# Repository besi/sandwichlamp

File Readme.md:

# Sandwich Lamp

## Pinout

| Pin | Function     |
|-----|--------------|
| 13  | Enable 12V   |
| 18  | Neopixel     |
| 14  | Touch 1      |
| 32  | Touch 2      |
| 4   | Touch 3      |
| 34  | Button 1     |
| 33  | Button 2     |
| 39  | Button 3     |
| 36  | Button 4     |
| 35  | Button X     |
| 27  | Radar TX     |
| 12  | Radar RX     |
| 19  | I2C SCL      |
| 23  | I2C SDA      |
| 16  | Battery Sens |
| 2   | Brightness   |
| 5   | Onboard LED  |
| 0   | OneWire      |

## Installation

```
import mip
mip.install("github:robert-hh/BME280")
```

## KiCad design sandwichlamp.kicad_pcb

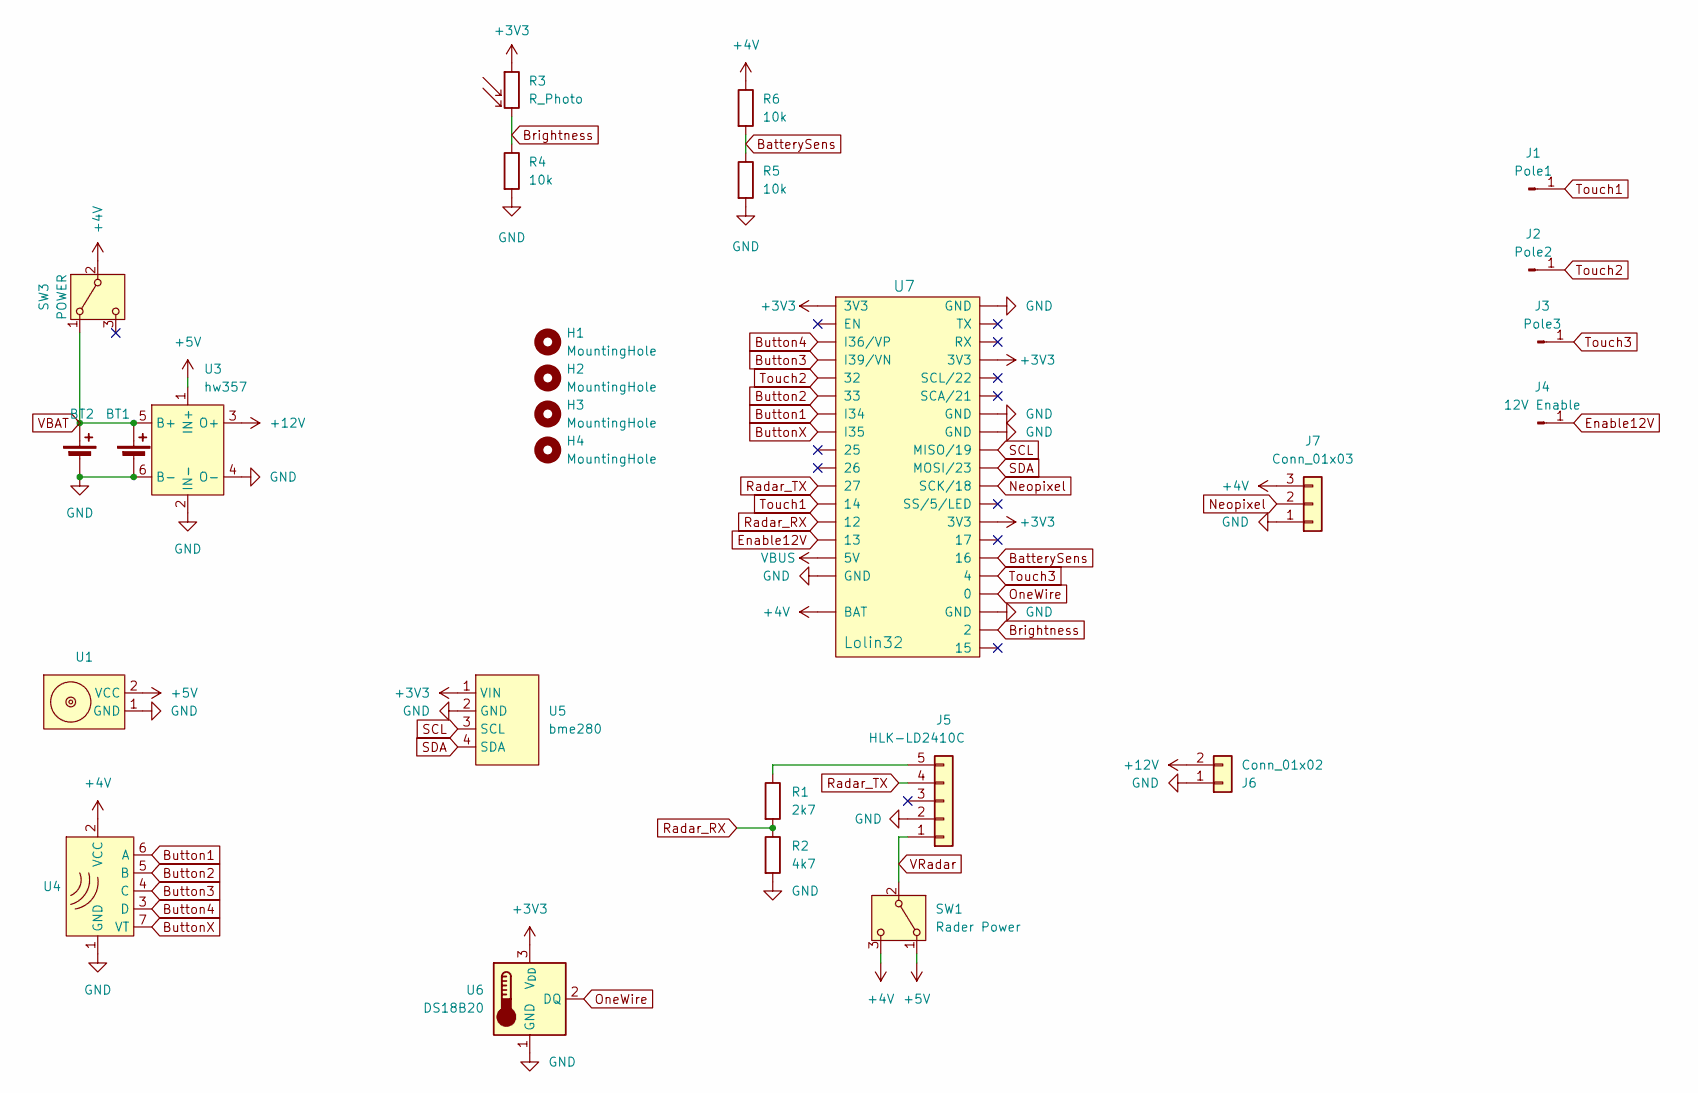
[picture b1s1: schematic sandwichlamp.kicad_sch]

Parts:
BT1: Battery_Cell; JST_PH_S2B-PH-SM4-TB_1x02-1MP_P2.00mm_Horizontal
BT2: Battery_Cell; JST_PH_B2B-PH-K_1x02_P2.00mm_Vertical
H1, H2, H3, H4: MountingHole; MountingHole_3.2mm_M3
J1: Pole1; MountingHole_4.3mm_M4_ISO7380_Pad_TopOnly
J2: Pole2; MountingHole_4.3mm_M4_ISO7380_Pad_TopOnly
J3: Pole3; MountingHole_4.3mm_M4_ISO7380_Pad_TopOnly
J4: 12V Enable; PinHeader_1x01_P2.54mm_Vertical
J5: HLK-LD2410C; PinHeader_1x05_P2.54mm_Vertical
J6: Conn_01x02; PinHeader_1x02_P2.54mm_Vertical
J7: Conn_01x03; PinHeader_1x03_P2.54mm_Vertical
R1: 2k7; R_Axial_DIN0207_L6.3mm_D2.5mm_P7.62mm_Horizontal
R2: 4k7; R_Axial_DIN0207_L6.3mm_D2.5mm_P7.62mm_Horizontal
R3: R_Photo; R_LDR_5.0x4.1mm_P3mm_Vertical
R4, R5, R6: 10k; R_0805_2012Metric_Pad1.20x1.40mm_HandSolder
SW1: Rader Power; PinHeader_1x03_P2.54mm_Vertical
SW3: POWER; as12ap
U1: magnetic-charger
U3: hw357
U4: RX480E; radio-receiver
U5: bme280
U6: DS18B20; TO-92L_Inline_Wide
U7: Lolin32; lolin32

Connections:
+3V3: R3.1, U5.1 (VIN), U6.3 (V_{DD}), U7.1 (3V3), U7.20 (3V3), U7.29 (3V3)
+4V: J7.3, R6.1, SW1.3 (C), SW3.2 (B), U4.2 (VCC), U7.37 (BAT)
+5V: SW1.1 (A), U1.2 (VCC), U3.1 (IN+)
+12V: J6.2, U3.3 (O+)
BatterySens: R5.1, R6.2, U7.31 (16)
Brightness: R3.2, R4.1, U7.35 (2)
Button1: U4.6 (A), U7.7 (I34)
Button2: U4.5 (B), U7.6 (33)
Button3: U4.4 (C), U7.4 (I39/VN)
Button4: U4.3 (D), U7.3 (I36/VP)
ButtonX: U4.7 (VT), U7.8 (I35)
Enable12V: J4.1, U7.14 (13)
GND: BT1.1 (-), BT2.2 (-), J5.2, J6.1, J7.1, R2.2, R4.2, R5.2, U1.1 (GND), U3.2 (IN-), U3.4 (O-), U3.6 (B-), U4.1 (GND), U5.2 (GND), U6.1 (GND), U7.16 (GND), U7.17 (GND), U7.23 (GND), U7.24 (GND), U7.34 (GND)
Neopixel: J7.2, U7.27 (SCK/18)
unnamed: J5.5, R1.1
OneWire: U6.2 (DQ), U7.33 (0)
Radar_RX: R1.2, R2.1, U7.13 (12)
Radar_TX: J5.4, U7.11 (27)
SCL: U5.3 (SCL), U7.25 (MISO/19)
SDA: U5.4 (SDA), U7.26 (MOSI/23)
Touch1: J1.1, U7.12 (14)
Touch2: J2.1, U7.5 (32)
Touch3: J3.1, U7.32 (4)
VBAT: BT1.2 (+), BT2.1 (+), SW3.1 (A), U3.5 (B+)
VBUS: U7.15 (5V)
VRadar: J5.1, SW1.2 (B)

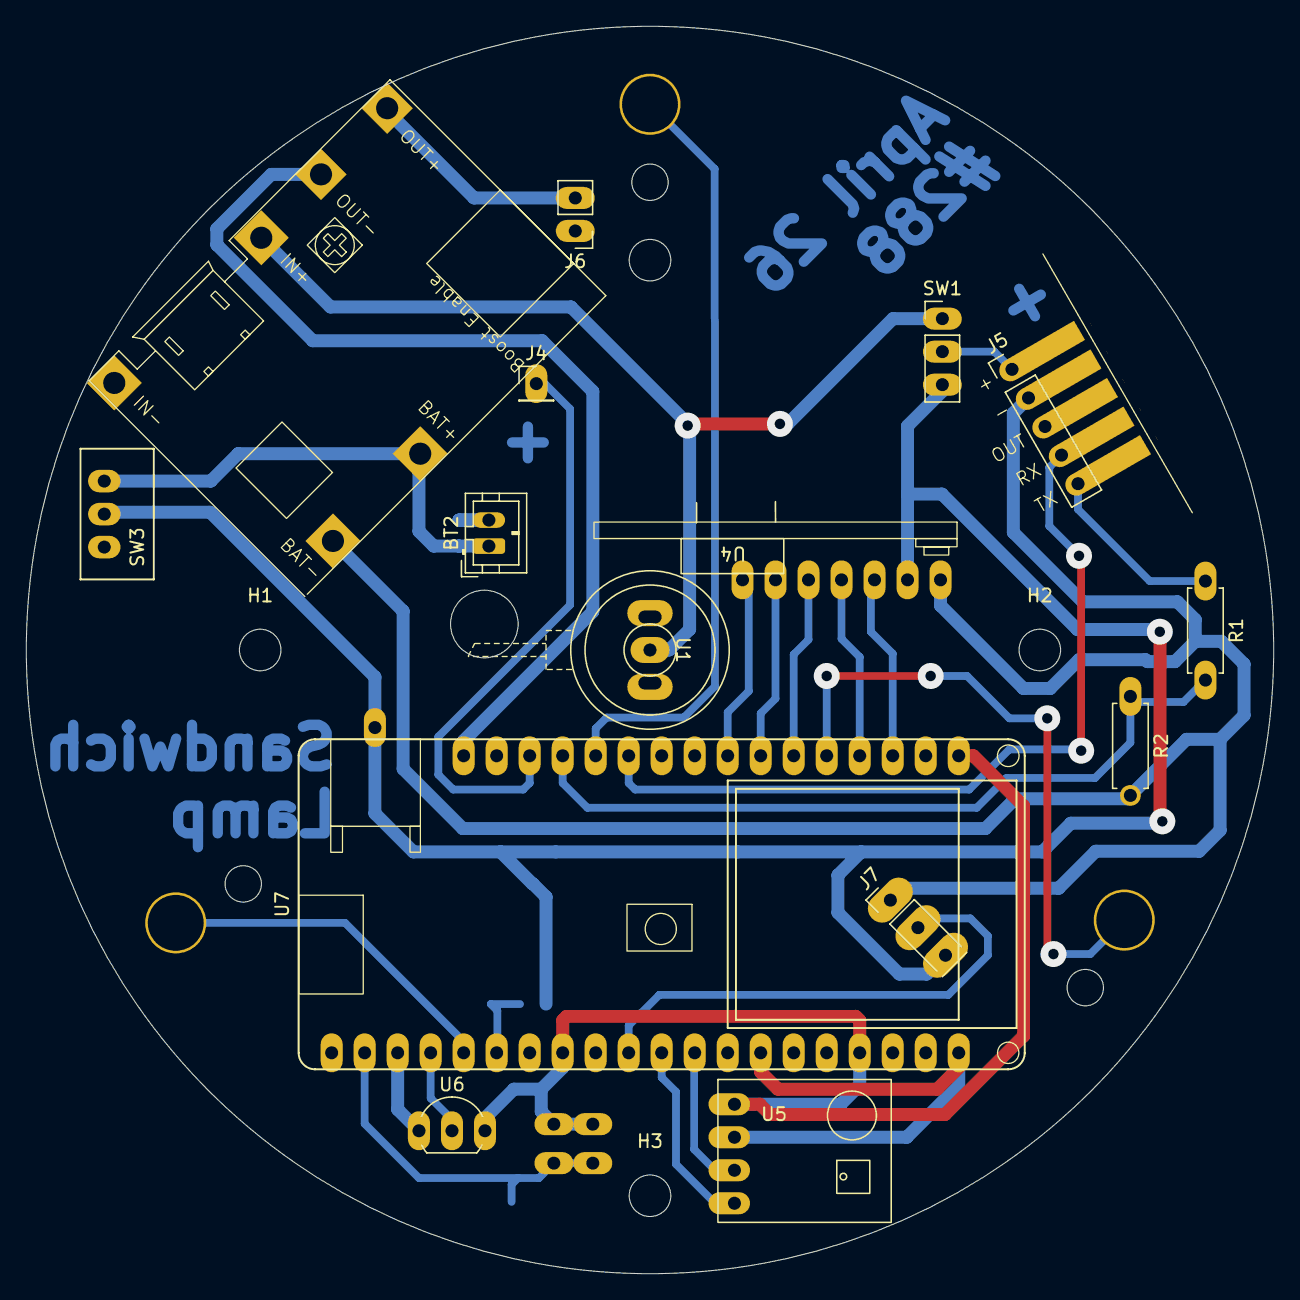
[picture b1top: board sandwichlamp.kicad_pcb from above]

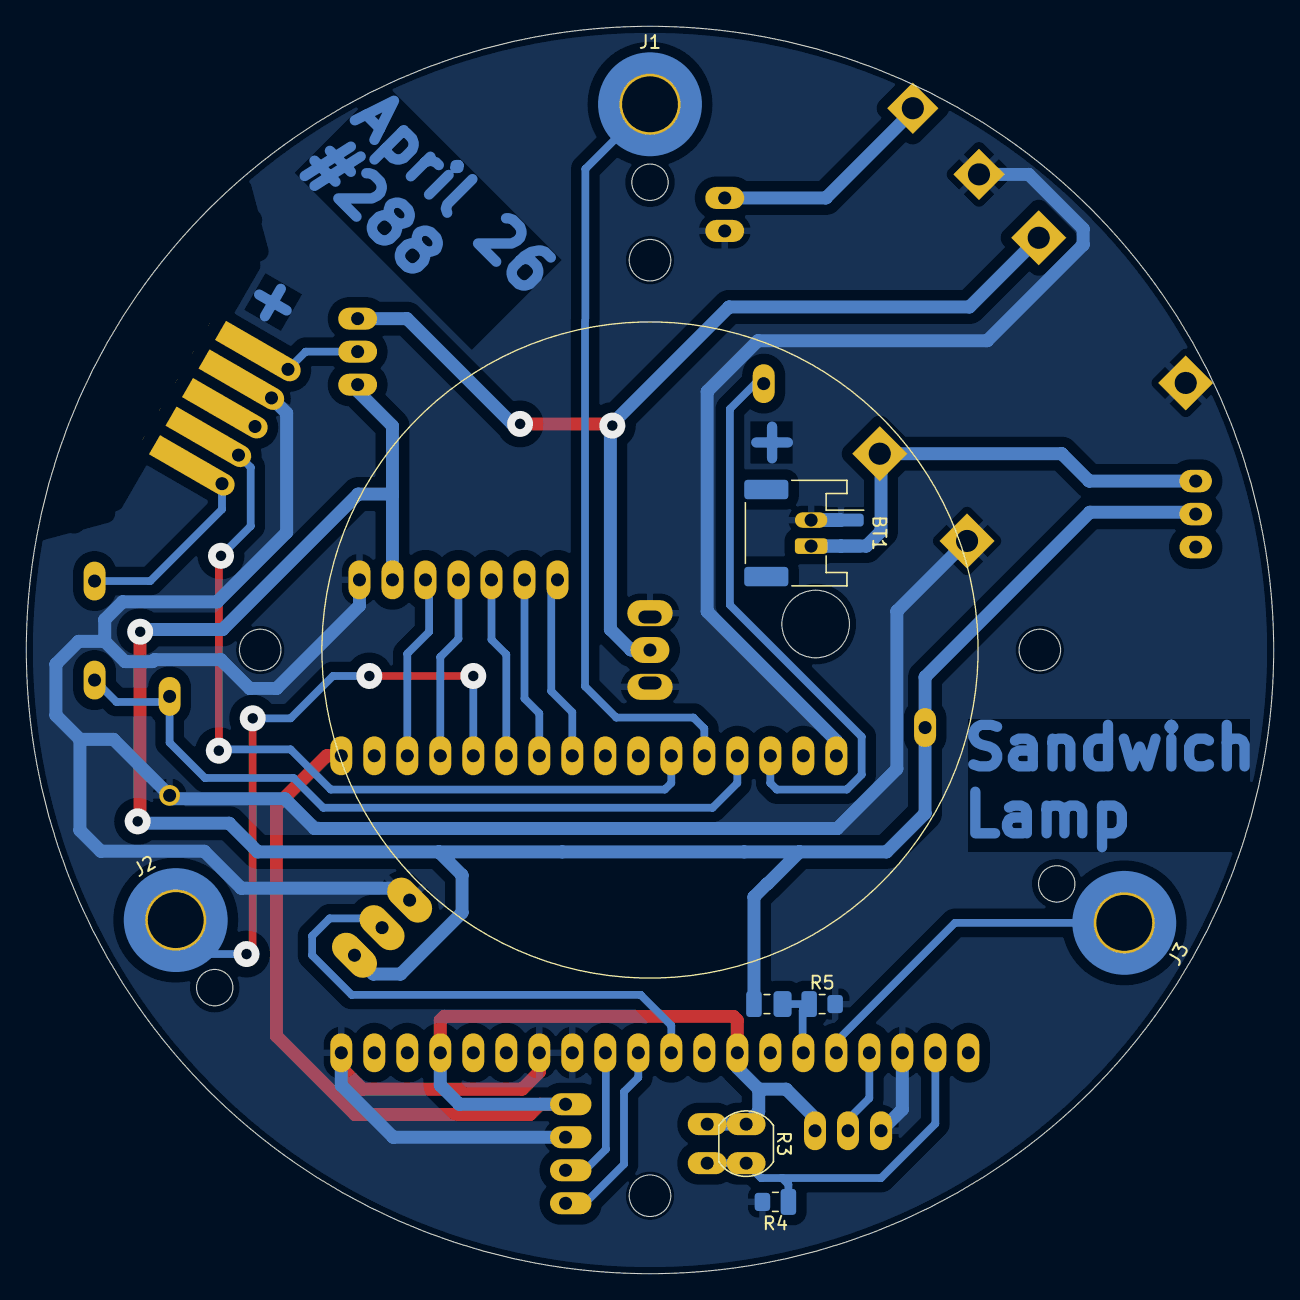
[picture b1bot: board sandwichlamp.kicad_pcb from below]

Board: 2 copper layers, 96.0 x 96.0 mm, 27 parts (8 on the bottom side), 25 nets.

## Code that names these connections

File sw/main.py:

from machine import Pin, PWM
import asyncio
from primitives import ESP32Touch, Pushbutton
from  neopixel import NeoPixel
pixelCount = 44
np = NeoPixel(Pin(18), pixelCount)

touch1_pin = 14
touch2_pin = 32
touch3_pin = 4

button_a_pin = 34
button_b_pin = 33
button_c_pin = 39
button_d_pin = 36

enable12v_pin = 13

pwm_start = 610
pwm_end = 1020
pwm_steps = (pwm_end-pwm_start)/20
pwm = PWM(Pin(enable12v_pin), freq=1000)          # create a PWM object on a pin


mode_max = 2
mode = 1
intensity = 10 # 0 .. 20

def down():
    global intensity
    intensity = max(0, intensity -1 )
    print(f"Down {intensity}")

    update_mode(False)

def up():
    global intensity
    intensity = min(20, intensity + 1)
    print(f"Up {intensity}")

    update_mode(False)

def update_mode(modeChanged = True):
    global mode
    global intensity
    
    print(f"Mode = {mode}")
    if mode != 1 and modeChanged:
        pwm.duty(0)
    if mode == 1:
        if modeChanged and pwm.duty() > 1:
            pwm.duty(0)
        else:
            pwm.duty(int(intensity * pwm_steps)+pwm_start)
        

def change_mode():
    global mode
    if mode == mode_max:
        mode = 1
    else:
        mode += 1
    update_mode()
            
def button(number):
    print(f"Pressed Button #{number}")
    if number == 1:
        np.fill((25,0,0))
    elif number == 2:
        np.fill((0,25,0))
    elif number == 3:
        np.fill((0,0,25))
    elif number == 4:
        np.fill((0,0,0))
    np.write()
    
async def main():
    ESP32Touch.threshold(95)
    t1 = ESP32Touch(Pin(touch1_pin), suppress=True)
    t1.release_func(lambda : down())
    t2 = ESP32Touch(Pin(touch2_pin), suppress=True)
    t2.release_func(lambda : change_mode())
    t3 = ESP32Touch(Pin(touch3_pin), suppress=True)
    t3.release_func(lambda : up())

    pb1 = Pushbutton(Pin(button_a_pin, Pin.IN, Pin.PULL_UP))
    pb1.press_func(button, (1,))
    pb2 = Pushbutton(Pin(button_b_pin, Pin.IN, Pin.PULL_UP))
    pb2.press_func(button, (2,))
    pb3 = Pushbutton(Pin(button_c_pin, Pin.IN, Pin.PULL_UP))
    pb3.press_func(button, (3,))
    pb4 = Pushbutton(Pin(button_d_pin, Pin.IN, Pin.PULL_UP))
    pb4.press_func(button, (4,))

    update_mode()
    while True:
        await asyncio.sleep(1)

asyncio.run(main())

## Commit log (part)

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2026-04-01 Update PCB
2026-04-01 Add radar sensor
2026-04-02 Add BME280 sensor
2026-04-02 Add Radio receiver module
2026-04-02 Update magnetic charger lib which shows the outline of the cable
2026-04-02 Align the radar with the cable
2026-04-02 Add BME280 and radio-receiver and continue with the placement of the components
2026-04-02 Add new esp footprint
2026-04-02 Add the new Lolin32 footprint
2026-04-02 Update Lolin Footprint
2026-04-03 Add power switch and power switch for the radar
2026-04-03 Add battery pad to the Lolin where the battery voltage can be taken for the ESP
2026-04-03 Add M3 mounting holes
2026-04-03 Add a light sensor and the labels for the existing components
2026-04-03 Add battery sensing
2026-04-03 Add Neopixel footprint and do the preliminary routing
2026-04-03 Routing
2026-04-03 Relocate the light sensor so that it can actually sense some light from the top of the lamp
2026-04-05 Make sure input-only pins are used as such
2026-04-05 Fix the touch buttons
2026-04-05 Cleanup schematic and pcb
2026-04-05 Test the hardware
2026-04-05 Disconnect the two 5V nets from one another
2026-04-05 Relocate the logo
2026-04-05 Test the radar
2026-04-05 Test the Neopixel
2026-04-06 Thicker GND trace for the temperature sensor
2026-04-07 Run DRC
2026-04-09 Add rudimentary DS18b20 test
2026-04-10 Prepare for plotting
2026-04-10 Remove the obsolete c3-pico as well as the wemos d1 mini git sub module
2026-04-11 Reverse the polarity of the SMD Battery Connector
2026-04-11 Add test code for the bme280 sensor
2026-04-11 Hide the pin numbers of the ESP32 in schematic since it is very confusing with the GPIO numbers being shown at the same time
2026-04-11 Update the PWM test so that it runs in a loop
2026-04-11 Add BME Library
2026-04-11 Switch the radar TX RX pins
2026-04-11 Slightly change the radar library in order to be able to plot the distance
2026-04-11 Make the touch test more responsive
2026-04-21 Test the 12V lamp with both on/off and PWM
2026-04-21 Show a rainbow for testing the neopixels
2026-04-22 Increase the timeout for the LD2410 sensor
2026-04-22 Don't set a maximum gate (0-8) which would limit the responsive ness of the sensor
2026-04-22 Refrain from setting a sensitivity for a specific gate
2026-04-22 Clean up radar test
2026-04-30 Initial state of the main.py
2026-04-30 Fix the main.py code so that the lamp can be toggled
2026-04-30 Make the neopixel code async-friendly
2026-05-04 Update the main program in order to run several different modes
